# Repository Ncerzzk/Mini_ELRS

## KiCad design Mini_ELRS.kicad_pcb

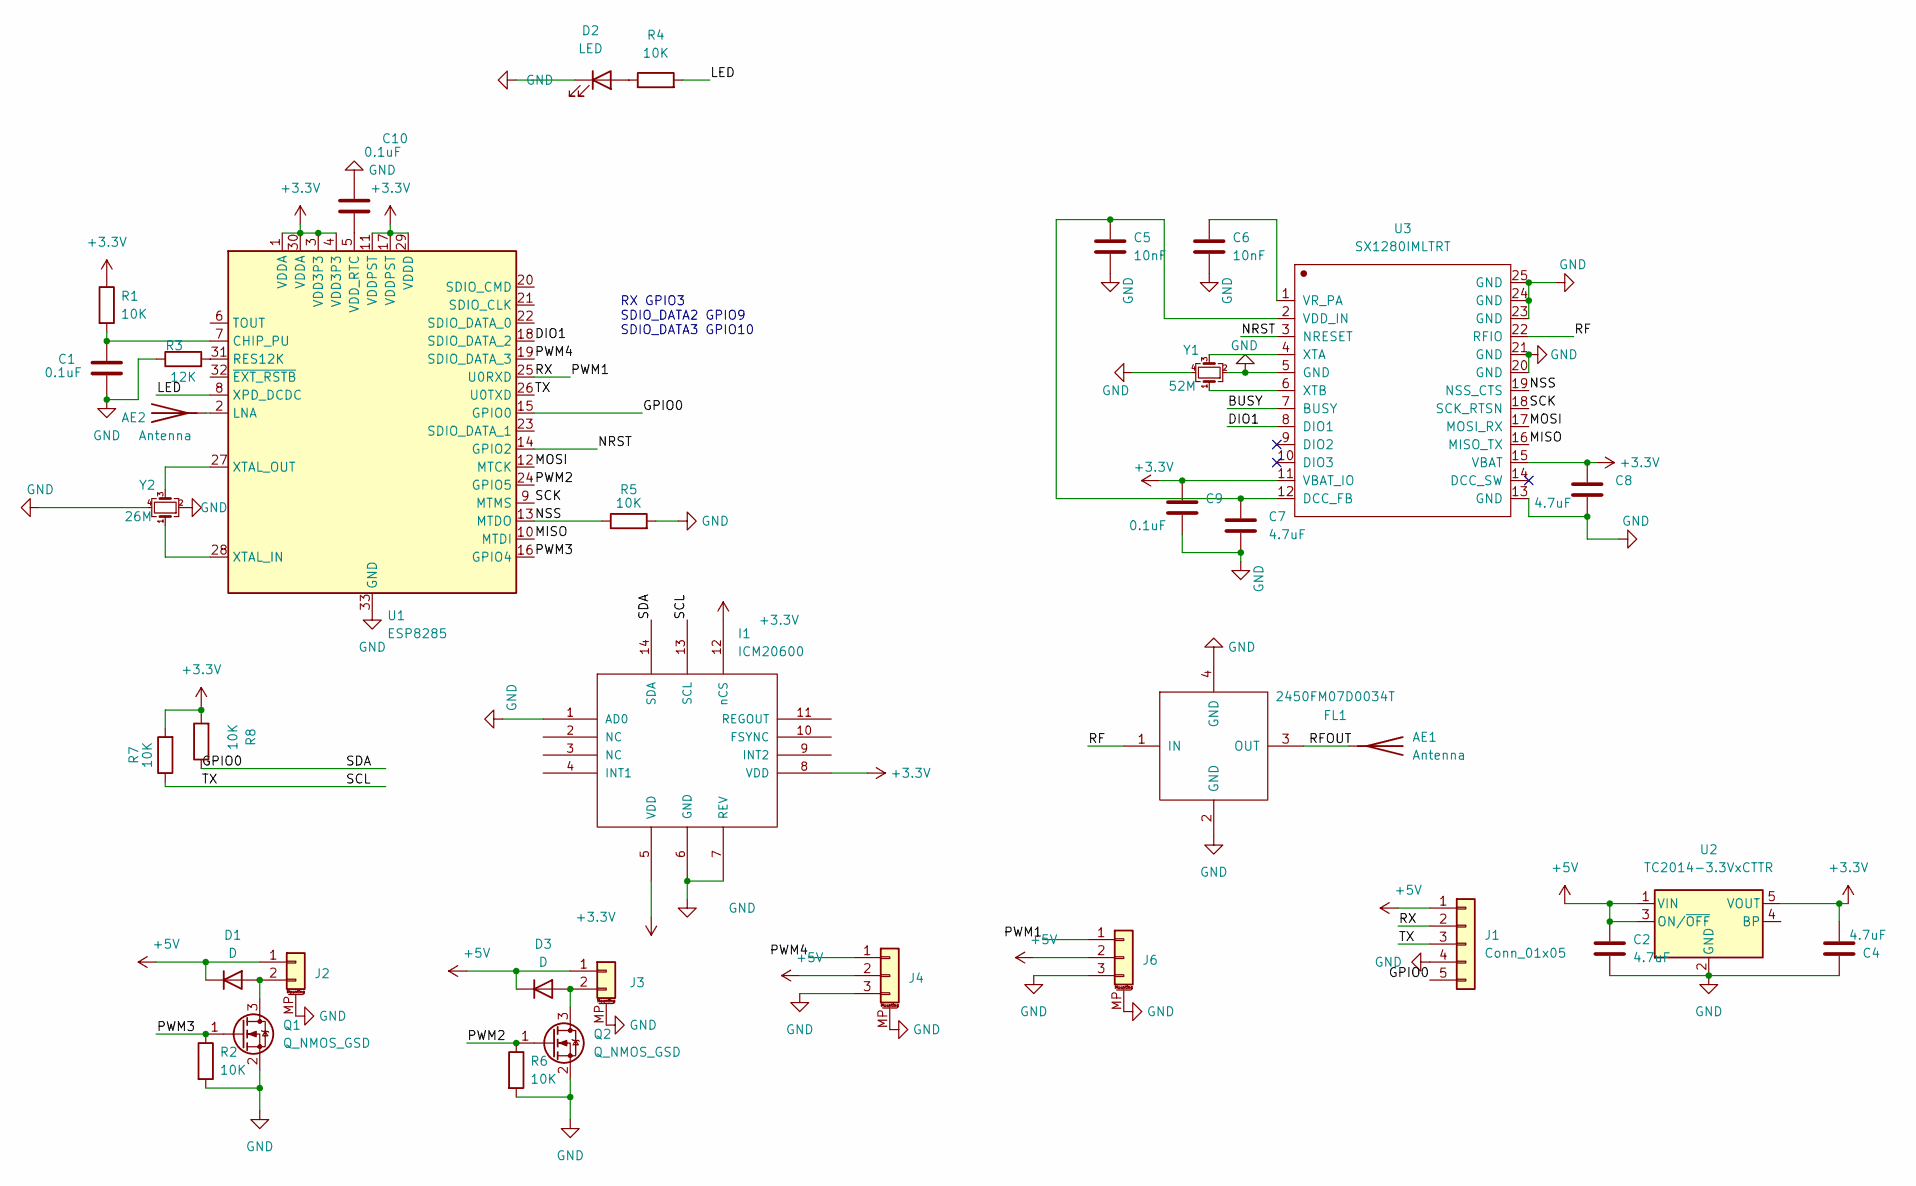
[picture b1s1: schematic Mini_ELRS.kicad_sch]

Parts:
AE1: Antenna; Johanson_2450AT43F0100
AE2: Antenna; C_1206_3216Metric
C1, C9, C10: 0.1uF; C_0402_1005Metric
C2, C4, C7, C8: 4.7uF; C_0402_1005Metric
C5, C6: 10nF; C_0402_1005Metric
D1, D3: D; D_SOD-323
D2: LED; LED_0603_1608Metric
FL1: 2450FM07D0034T; FILTER-SMD_4P-L1.0-W0.5-L
I1: ICM20600; Bosch_LGA-14_3x2.5mm_P0.5mm
J1: Conn_01x05; PinHeader_1x05_P2.54mm_Vertical
J2, J3: Conn_01x02_MountingPin; Molex_CLIK-Mate_502386-0270_1x02-1MP_P1.25mm_Horizontal
J4, J6: Conn_01x03_MountingPin; Molex_CLIK-Mate_502386-0370_1x03-1MP_P1.25mm_Horizontal
Q1, Q2: Q_NMOS_GSD; SOT-23
R1, R2, R4, R5, R6, R7, R8: 10K; R_0402_1005Metric
R3: 12K; R_0402_1005Metric
U1: ESP8285; QFN-32-1EP_5x5mm_P0.5mm_EP3.45x3.45mm
U2: TC2014-3.3VxCTTR; SOT-23-5
U3: SX1280IMLTRT; QFN-24-1EP_4x4mm_P0.5mm_EP2.65x2.65mm
Y1: 52M; Crystal_SMD_2520-4Pin_2.5x2.0mm
Y2: 26M; Crystal_SMD_2520-4Pin_2.5x2.0mm

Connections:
+3V3: C4.1, C8.1, C9.1, I1.5 (VDD), I1.8 (VDD), I1.12 (nCS), R1.1, R7.2, R8.2, U1.1 (VDDA), U1.3 (VDD3P3), U1.4 (VDD3P3), U1.11 (VDDPST), U1.17 (VDDPST), U1.29 (VDDD), U1.30 (VDDA), U2.5 (VOUT), U3.11 (VBAT_IO), U3.15 (VBAT)
+5V: C2.1, D1.1 (K), D3.1 (K), J1.1, J2.1, J3.1, J4.2, J6.2, U2.1 (VIN), U2.3 (ON/~OFF)
/BUSY: U3.7 (BUSY)
/DIO1: U1.18 (SDIO_DATA_2), U3.8 (DIO1)
/GPIO0: I1.14 (SDA), J1.5, R8.1, U1.15 (GPIO0)
/LED: R4.2, U1.8 (XPD_DCDC)
/MISO: U1.10 (MTDI), U3.16 (MISO_TX)
/MOSI: U1.12 (MTCK), U3.17 (MOSI_RX)
/NRST: U1.14 (GPIO2), U3.3 (NRESET)
/NSS: R5.1, U1.13 (MTDO), U3.19 (NSS_CTS)
/PWM1: J1.2, J6.1, U1.25 (U0RXD)
/PWM2: Q2.1 (G), R6.1, U1.24 (GPIO5)
/PWM3: Q1.1 (G), R2.1, U1.16 (GPIO4)
/PWM4: J4.1, U1.19 (SDIO_DATA_3)
/RF: FL1.1 (IN), U3.22 (RFIO)
/RFOUT: AE1.1 (A), FL1.3 (OUT)
/SCK: U1.9 (MTMS), U3.18 (SCK_RTSN)
/TX: I1.13 (SCL), J1.3, R7.1, U1.26 (U0TXD)
GND: C1.2, C2.2, C4.2, C5.2, C6.2, C7.2, C8.2, C9.2, C10.1, D2.1 (K), FL1.2 (GND), FL1.4 (GND), I1.1 (AD0), I1.6 (GND), I1.7 (REV), J1.4, J2.MP (MountPin), J3.MP (MountPin), J4.3, J4.MP (MountPin), J6.3, J6.MP (MountPin), Q1.2 (S), Q2.2 (S), R2.2, R3.1, R5.2, R6.2, U1.33 (GND), U2.2 (GND), U3.5 (GND), U3.13 (GND), U3.20 (GND), U3.21 (GND), U3.23 (GND), U3.24 (GND), U3.25 (GND), Y1.2, Y1.4, Y2.2, Y2.4
unnamed: C1.1, R1.2, U1.7 (CHIP_PU)
unnamed: C5.1, C7.1, U3.2 (VDD_IN), U3.12 (DCC_FB)
unnamed: C6.1, U3.1 (VR_PA)
unnamed: C10.2, U1.5 (VDD_RTC)
unnamed: D2.2 (A), R4.1
unnamed: D1.2 (A), J2.2, Q1.3 (D)
unnamed: D3.2 (A), J3.2, Q2.3 (D)
unnamed: R3.2, U1.31 (RES12K)
unnamed: AE2.1 (A), U1.2 (LNA)
unnamed: U1.27 (XTAL_OUT), Y2.3
unnamed: U1.28 (XTAL_IN), Y2.1
unnamed: U3.4 (XTA), Y1.3
unnamed: U3.6 (XTB), Y1.1

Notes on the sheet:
RX GPIO3 SDIO_DATA2 GPIO9 SDIO_DATA3 GPIO10

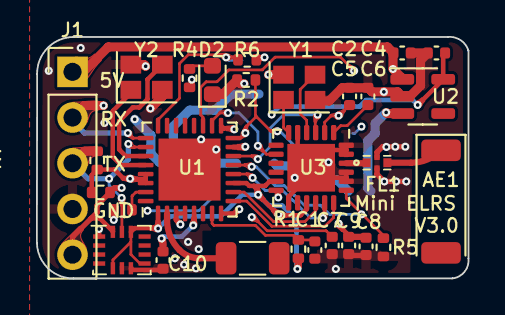
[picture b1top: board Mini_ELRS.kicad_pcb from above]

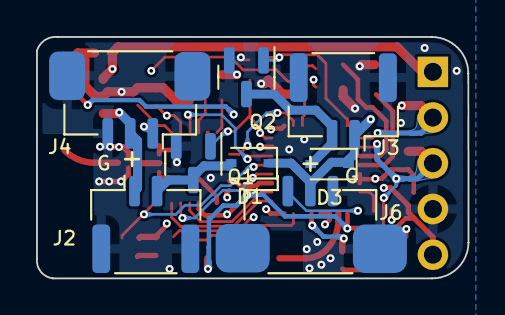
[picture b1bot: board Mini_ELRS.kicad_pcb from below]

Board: 4 copper layers, 24.0 x 13.4 mm, 36 parts (8 on the bottom side), 31 nets.

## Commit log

2024-04-14 add motor and servo interface
2024-04-29 fix wrong pwm pins
2024-05-23 update mcu to esp8285 rather than esp8266
2024-06-07 v2.2 add diode in motor interface
2024-06-16 3.0 add imu 42670
